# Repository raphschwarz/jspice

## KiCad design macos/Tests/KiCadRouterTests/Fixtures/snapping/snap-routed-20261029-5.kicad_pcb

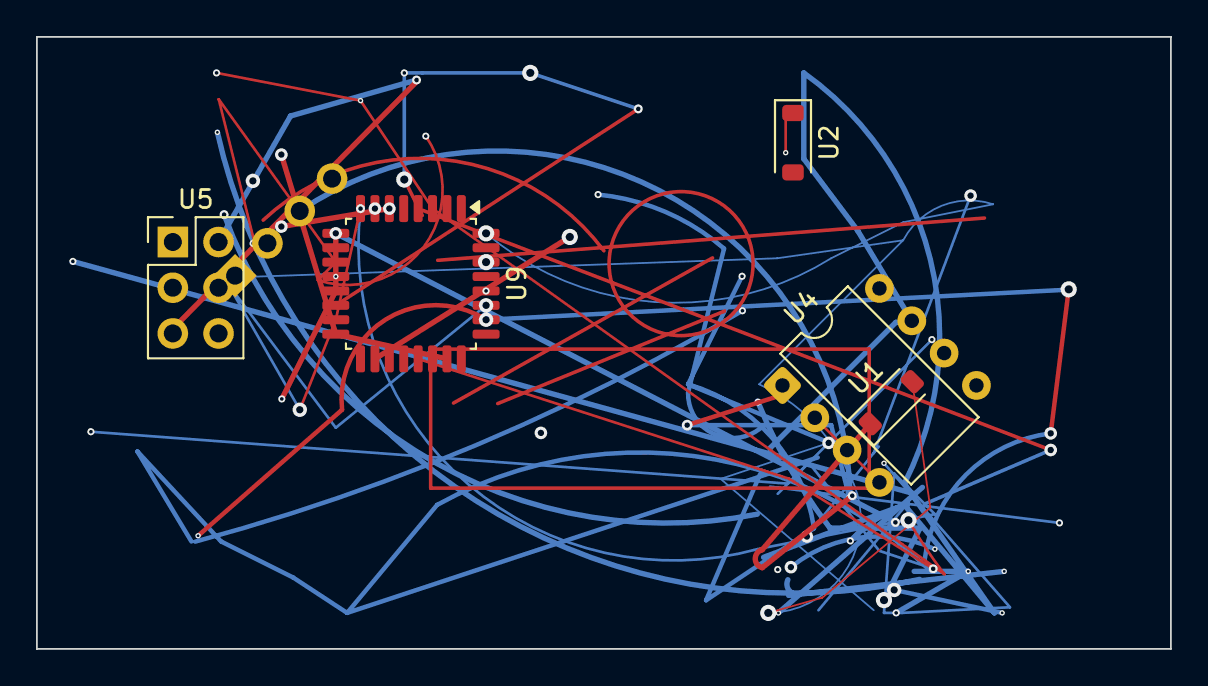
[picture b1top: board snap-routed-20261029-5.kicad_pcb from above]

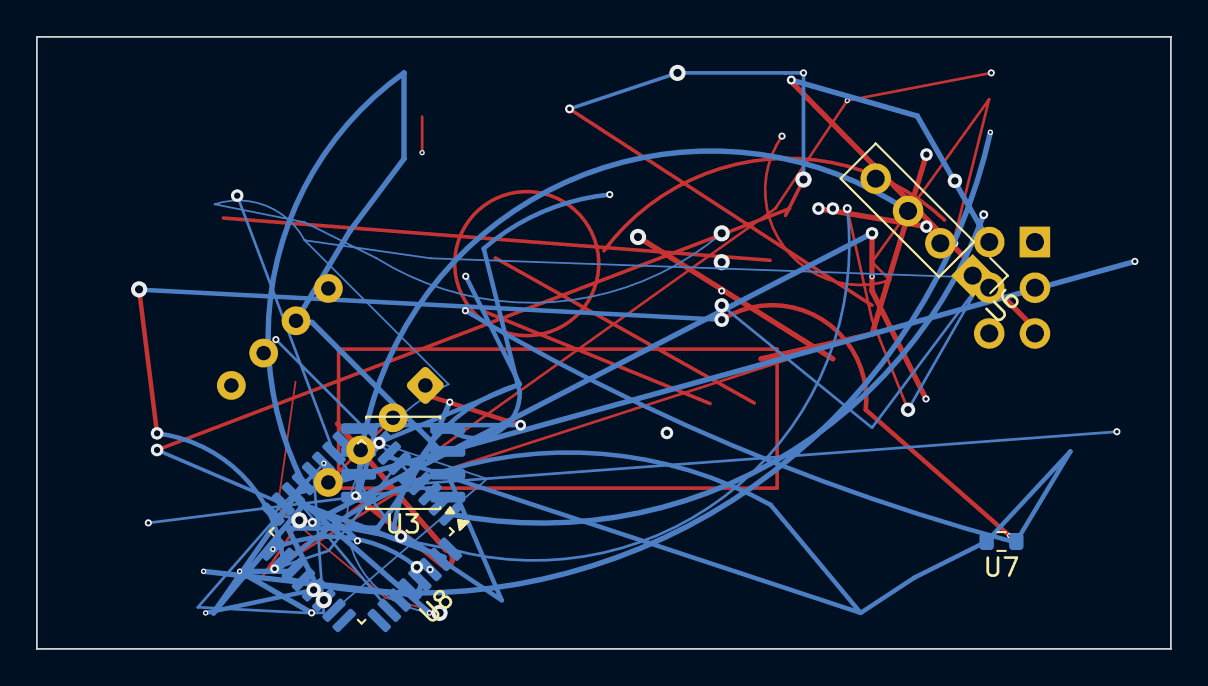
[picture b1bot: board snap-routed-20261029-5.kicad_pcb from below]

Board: 4 copper layers, 63.0 x 34.0 mm, 9 parts (4 on the bottom side), 10 nets.

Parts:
U1, U2: D_SOD-123
U3: SOIC-8_3.9x4.9mm_P1.27mm
U4: DIP-8_W7.62mm
U5: PinHeader_2x03_P2.54mm_Vertical
U6: PinHeader_1x04_P2.54mm_Vertical
U7: R_0603_1608Metric
U8, U9: LQFP-32_7x7mm_P0.8mm

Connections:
4K7_IN: U3.3, U4.7, U8.13, U8.31
+3V3: U3.1, U3.2, U4.3, U7.1, U7.2, U8.7, U8.18, U9.26, U9.30
/sub/CLK2: U1.1, U6.3, U8.19, U8.28, U8.29, U9.9, U9.13, U9.18
/sub/clk: U4.2, U4.4, U8.3, U8.6, U9.21
D7: U3.4, U3.8, U4.1, U8.17, U8.21, U8.30, U9.10, U9.20
GND: U8.15, U9.4, U9.7, U9.12, U9.14
N2: U2.1, U4.5, U5.4, U8.4, U8.10, U8.11, U8.12, U8.16, U8.32, U9.8, U9.15, U9.27
PWR_5V: U1.2, U3.7, U6.1, U8.8, U8.23, U9.1, U9.32
R1: U5.3, U8.20, U8.26, U9.3, U9.11, U9.28
R10: U5.2, U5.5, U5.6, U6.4, U8.1, U8.14, U8.22, U9.6, U9.16, U9.23
